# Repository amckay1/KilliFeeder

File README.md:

# KilliFeeder

## Components
1) Hardware
2) Software
3) Julia package: https://github.com/amckay1/Killifeeder.jl

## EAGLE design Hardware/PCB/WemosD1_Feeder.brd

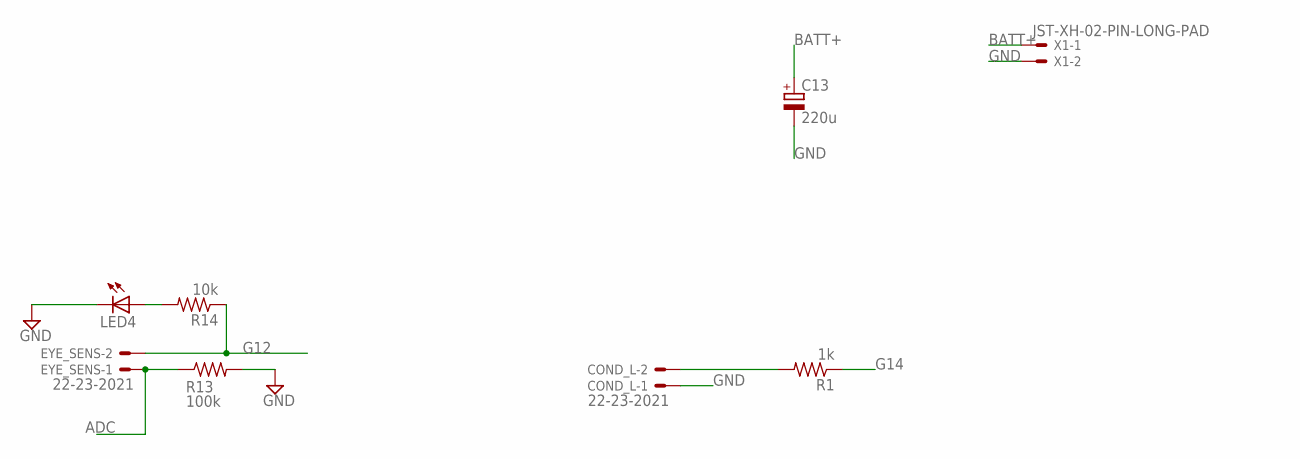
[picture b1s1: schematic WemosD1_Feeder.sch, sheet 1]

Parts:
C13: 220u; E2,5-7
COND_L: 22-23-2021
EYE_SENS: 22-23-2021
LED4: LED5MM
R1: 1k; R0603
R13: 100k; R0603
R14: 10k; R0603
X1: JST-XH-02-PIN-LONG-PAD; JST-XH-02-PACKAGE-LONG-PAD

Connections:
ADC: EYE_SENS.1, R13.1; also elsewhere on the board
BATT+: C13.+, X1.1; also elsewhere on the board
G12: EYE_SENS.2, R14.1; also elsewhere on the board
G14: R1.1; also elsewhere on the board
GND: C13.-, COND_L.1, LED4.K (C), R13.2, X1.2; also elsewhere on the board
unnamed: COND_L.2, R1.2
unnamed: LED4.A, R14.2

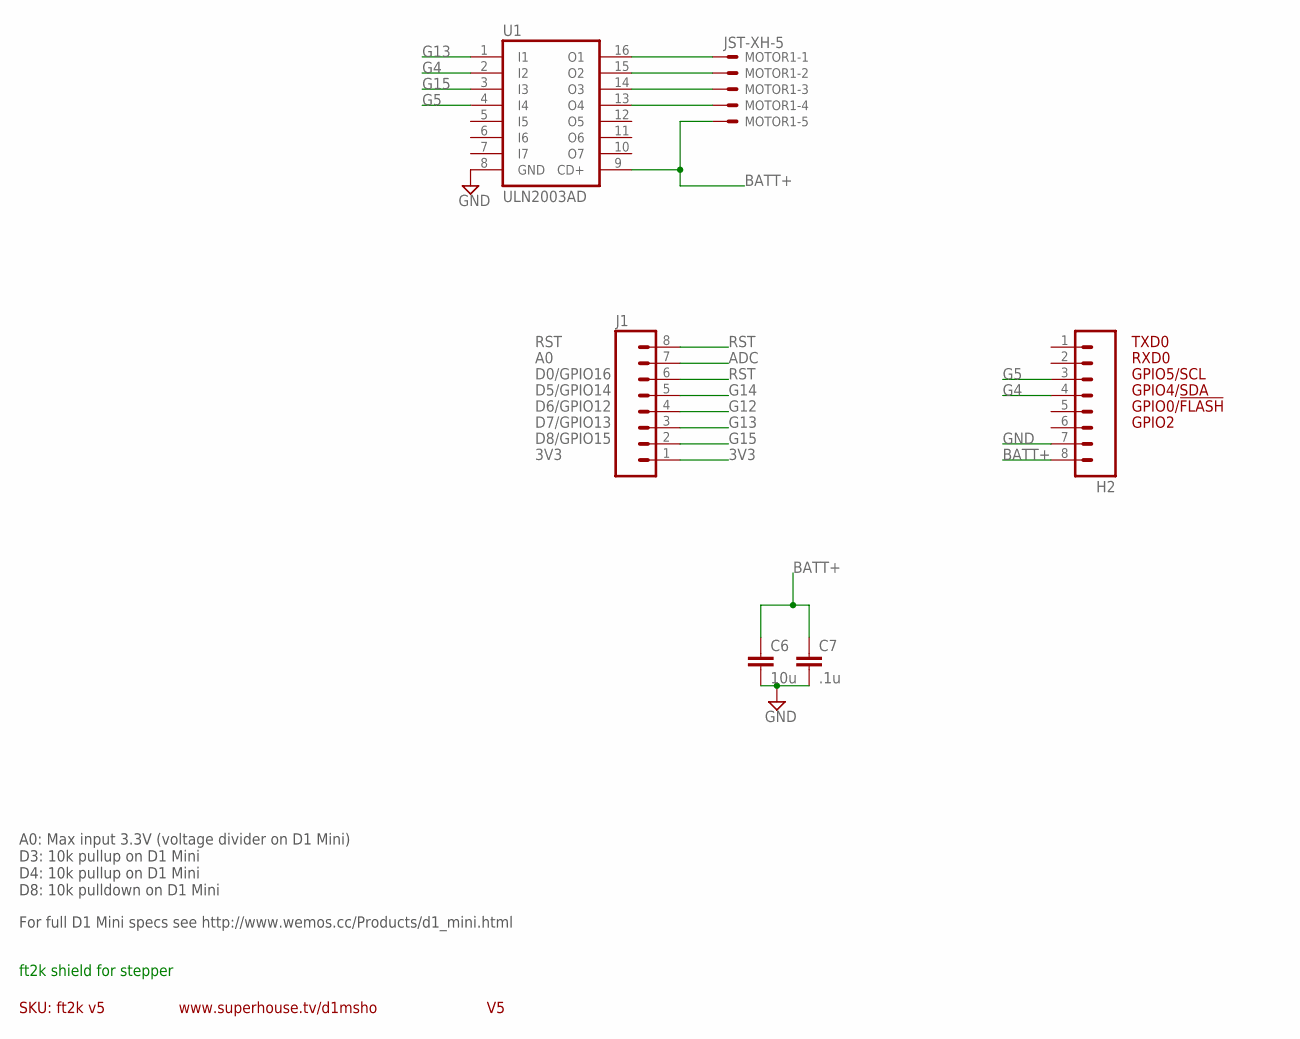
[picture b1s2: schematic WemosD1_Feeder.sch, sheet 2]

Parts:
C6: 10u; C0603
C7: .1u; C0603
H2: M08; 1X08
J1: M08; 1X08_ROUND
MOTOR1: JST-XH-5; JST-XH-5P
U1: ULN2003AD; SO16

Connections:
3V3: J1.1
ADC: J1.7; also elsewhere on the board
BATT+: C6.1, C7.1, H2.8, MOTOR1.P$5, U1.9 (CD+); also elsewhere on the board
G4: H2.4, U1.2 (I2)
G5: H2.3, U1.4 (I4)
G12: J1.4; also elsewhere on the board
G13: J1.3, U1.1 (I1)
G14: J1.5; also elsewhere on the board
G15: J1.2, U1.3 (I3)
GND: C6.2, C7.2, H2.7, U1.8 (GND); also elsewhere on the board
unnamed: MOTOR1.P$1, U1.16 (O1)
unnamed: MOTOR1.P$2, U1.15 (O2)
unnamed: MOTOR1.P$3, U1.14 (O3)
unnamed: MOTOR1.P$4, U1.13 (O4)
RST: J1.6, J1.8

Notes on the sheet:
GPIO2
GPIO0/!FLASH
GPIO4/SDA
GPIO5/SCL
RXD0
TXD0
SKU: ft2k v5
www.superhouse.tv/d1msho
A0: Max input 3.3V (voltage divider on D1 Mini) D3: 10k pullup on D1 Mini D4: 10k pullup on D1 Mini D8: 10k pulldown on D1 Mini
For full D1 Mini specs see http://www.wemos.cc/Products/d1_mini.html
ft2k shield for stepper
RST
D0/GPIO16
D5/GPIO14
D6/GPIO12
D7/GPIO13
D8/GPIO15
3V3

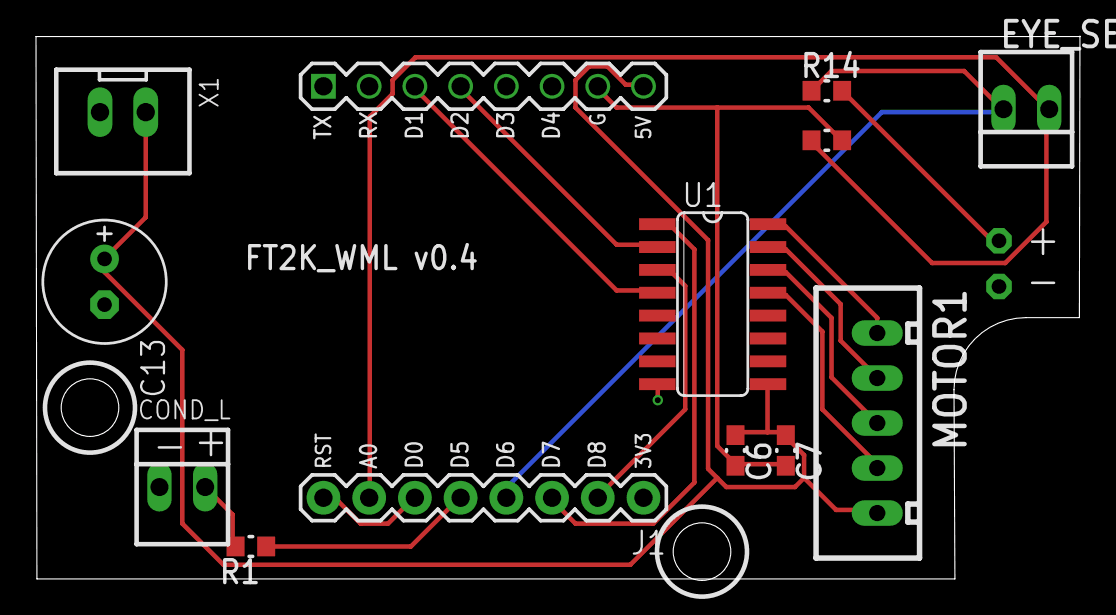
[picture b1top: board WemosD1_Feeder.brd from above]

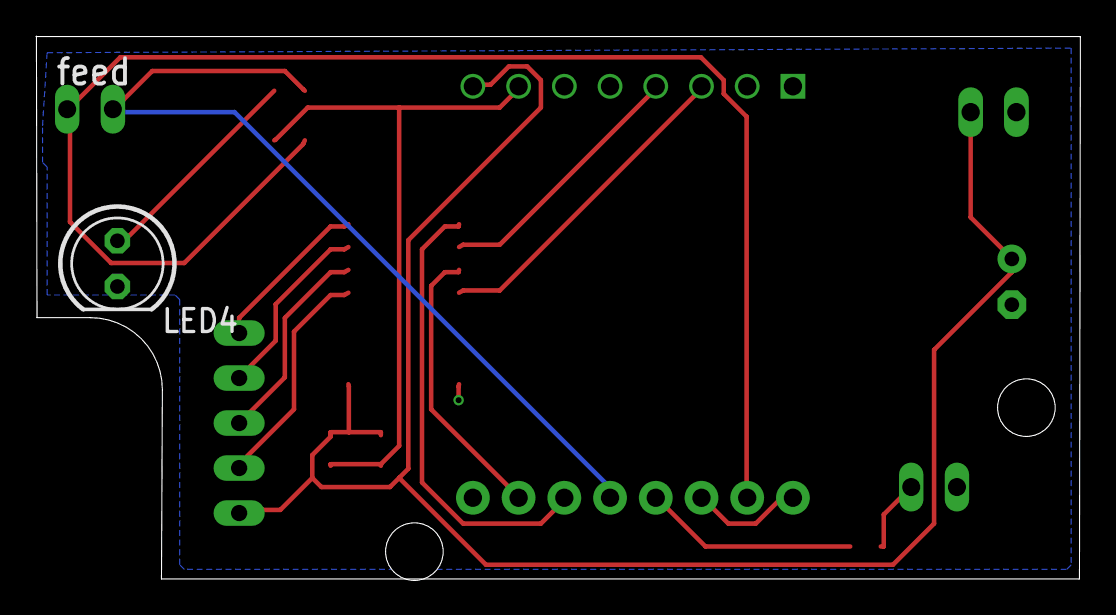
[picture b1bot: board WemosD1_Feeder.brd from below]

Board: 2 copper layers, 58.0 x 30.2 mm, 15 parts (2 on the bottom side), 16 nets.

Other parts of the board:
U$3: FT2K_PLATE

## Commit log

2020-06-01 init

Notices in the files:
parts and their libraries:
freetronics-original: Licensing: CC v3.0 Share-Alike You are welcome to use this library for commercial purposes.
SparkFun-Connectors: Licensing: Creative Commons ShareAlike 4.0 International - https://creativecommons.org/licenses/by-sa/4.0
